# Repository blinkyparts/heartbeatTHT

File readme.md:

# Heartbeat THT
Eine einfache Schaltung die eine LED sehr lange zum pulsieren bringt. Mit 3V sieht es sehr witzig aus, als ob die LED aus sich heraus platzen würde.

## Schaltungsidee
- https://www.maltepoeggel.de/?site=dauerblitzer
- Original von: https://www.b-kainka.de/bastel59.htm

## Bausatz kaufen
Natürlich könnt ihr auch wieder einen Bausatz bei uns im Onlineshop kaufen. Im Bausatz sind alle Bauteile und die Platine enthalten zum selbst löten :) [https://shop.blinkyparts.com/de/Heartbeat-Loetbausatz-Pulsierendes-LED-Herz-zum-Selbstloeten/blink23185](https://shop.blinkyparts.com/de/Heartbeat-Loetbausatz-Pulsierendes-LED-Herz-zum-Selbstloeten/blink23185)

## Platinendesign
- Originaldesign von: https://thenounproject.com/icon/heart-8097843/
- Created by ColorCombo from Noun Project
  Leicht angepasst. Wir haben eine Lizenz gekauft um den Künstler zu unterstützen, das solltest du auch machen!

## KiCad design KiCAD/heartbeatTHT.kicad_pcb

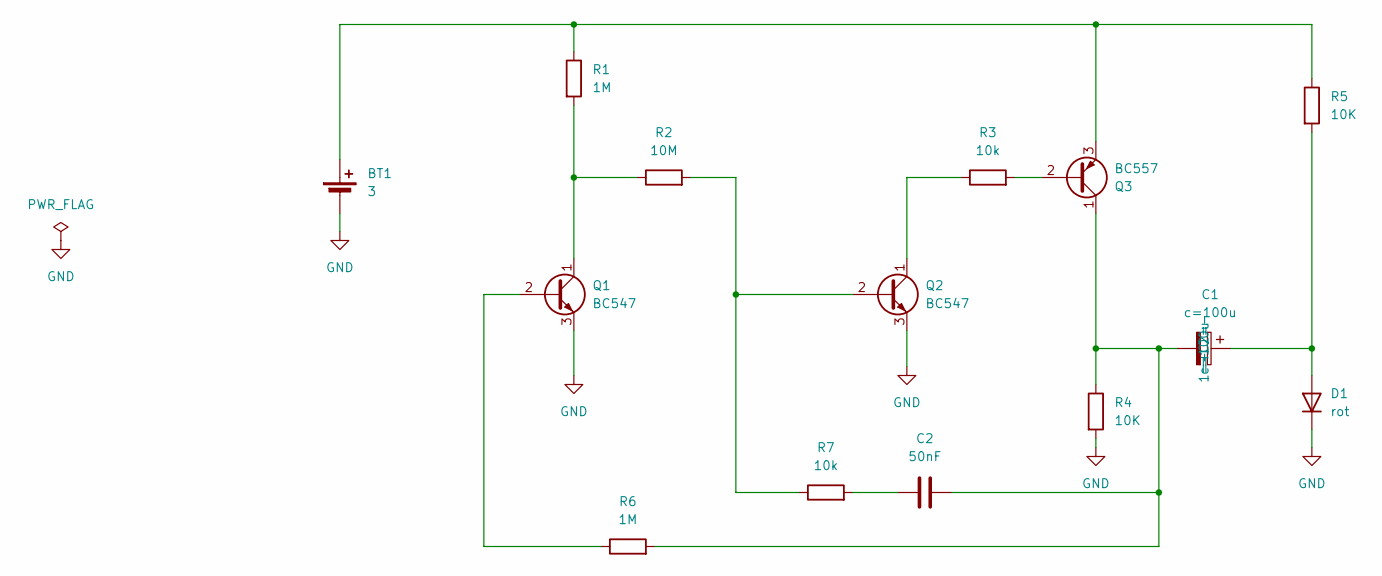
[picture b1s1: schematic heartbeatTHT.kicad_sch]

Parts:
BT1: 3; BatteryHolder_CR2032_schwarz
C1: c=100u; CP_Radial_D6.3mm_P2.50mm
C2: 50nF; C_Disc_D5.0mm_W2.5mm_P2.50mm
D1: rot; LED_D5.0mm
Q1, Q2: BC547; TO-92_HandSolder
Q3: BC557; TO-92_HandSolder
R1, R6: 1M; R_Axial_DIN0207_L6.3mm_D2.5mm_P7.62mm_Horizontal_handsolder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
R2: 10M; R_Axial_DIN0207_L6.3mm_D2.5mm_P7.62mm_Horizontal_handsolder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
R3, R7: 10k; R_Axial_DIN0207_L6.3mm_D2.5mm_P7.62mm_Horizontal_handsolder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
R4, R5: 10K; R_Axial_DIN0207_L6.3mm_D2.5mm_P7.62mm_Horizontal_handsolder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

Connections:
GND: BT1.2 (-), D1.1 (K), Q1.3 (E), Q2.3 (E), R4.2
unnamed: BT1.1 (+), Q3.3 (E), R1.1, R5.1
unnamed: C2.1, R7.2
unnamed: C1.1, D1.2 (A), R5.2
unnamed: Q1.2 (B), R6.1
unnamed: Q1.1 (C), R1.2, R2.1
unnamed: Q2.2 (B), R2.2, R7.1
unnamed: Q2.1 (C), R3.1
unnamed: Q3.2 (B), R3.2
unnamed: C1.2, C2.2, Q3.1 (C), R4.1, R6.2

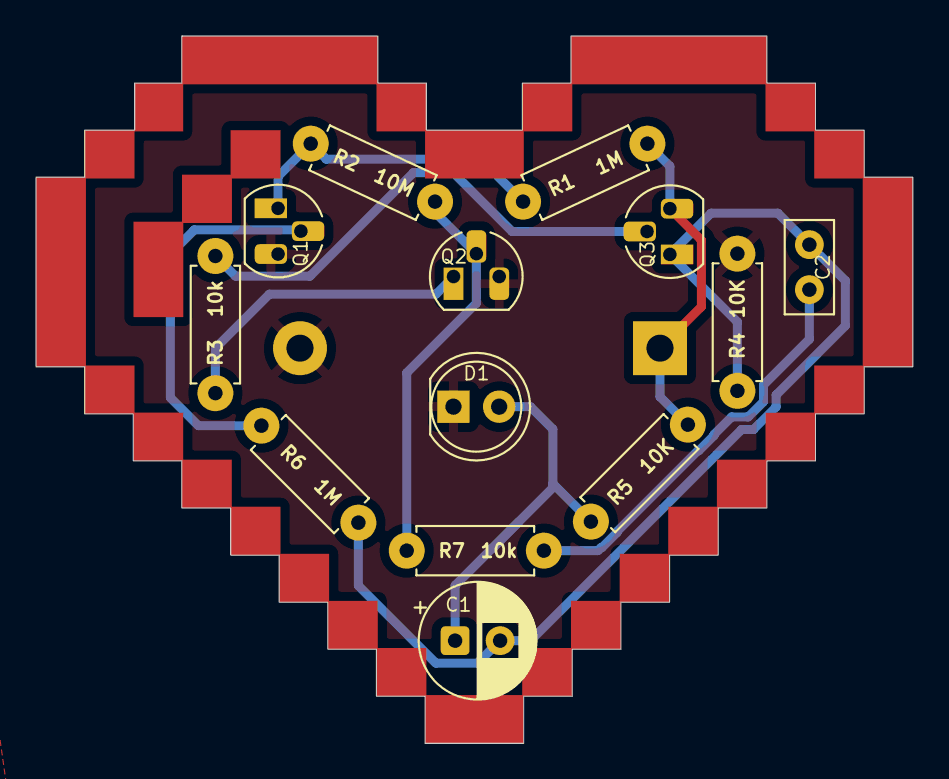
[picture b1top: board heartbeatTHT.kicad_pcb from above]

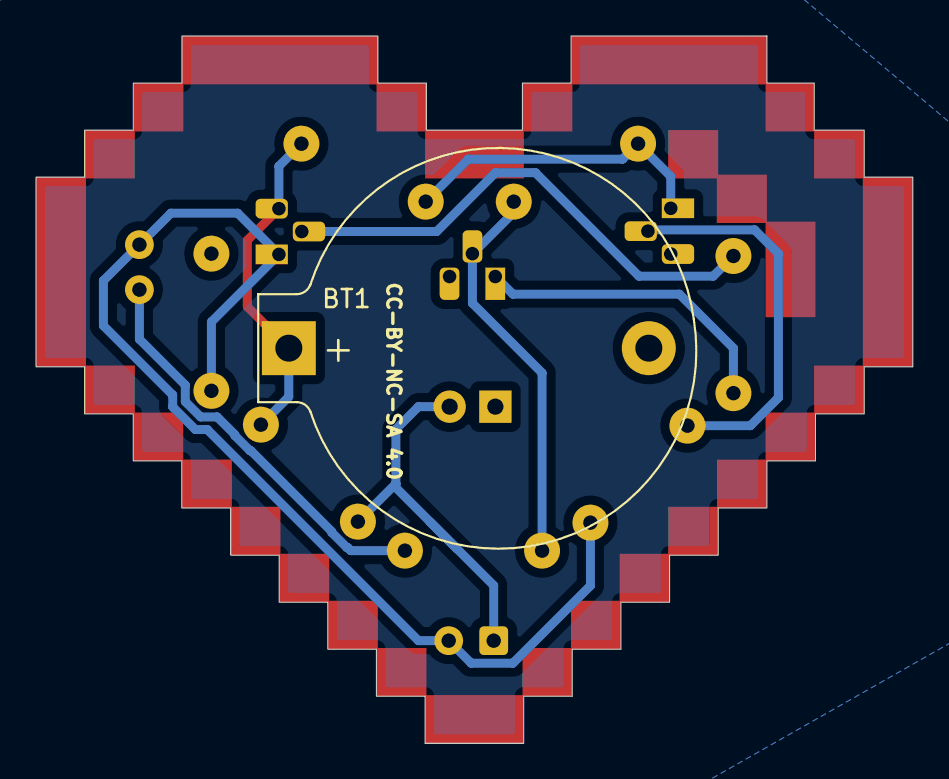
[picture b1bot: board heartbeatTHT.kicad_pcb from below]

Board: 2 copper layers, 48.7 x 39.3 mm, 18 parts (4 on the bottom side), 10 nets.

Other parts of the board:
blinkyparts_logo_5mm: G***; logo_5mm
ce-symbol_mask_3mm: G***; ce-icon_3mm
heart: G***; heart-pixel
weee-symbol_mask_3mm: G***; weee-icon_3mm

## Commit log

2026-01-06 added inital readme and gitignore
2026-01-06 inital commit for version 1.0 pre jörg
2026-01-06 added images
2026-01-11 fixed minor issues, added logo, added simulation
2026-01-11 added new images
2026-01-11 added extra readme for github
2026-01-11 updated text for readme
2026-01-18 updated github readme
2026-01-18 updated github readme agin
2026-02-18 changed 50uF to 100uF
2026-02-18 fixed typo
2026-02-18 added ibom
2026-02-19 added link to blinkyparts

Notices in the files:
KiCAD/heartbeatTHT.kicad_pcb:
CC-BY-NC-SA 4.0
